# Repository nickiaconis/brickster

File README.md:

BricksTer
=========

LEGO bricks controlled from terminal.

### Notice

[BricksTer has moved to BTbricks. Please follow this link for the list of new repositories.](https://github.com/BTbricks)

#### Android GUI (based on 8879 LEGO Power Functions Speed Remote Control)

#### Android GUI (based on 8885 LEGO Power Functions Remote Control)

#### Initial Prototype Demonstration

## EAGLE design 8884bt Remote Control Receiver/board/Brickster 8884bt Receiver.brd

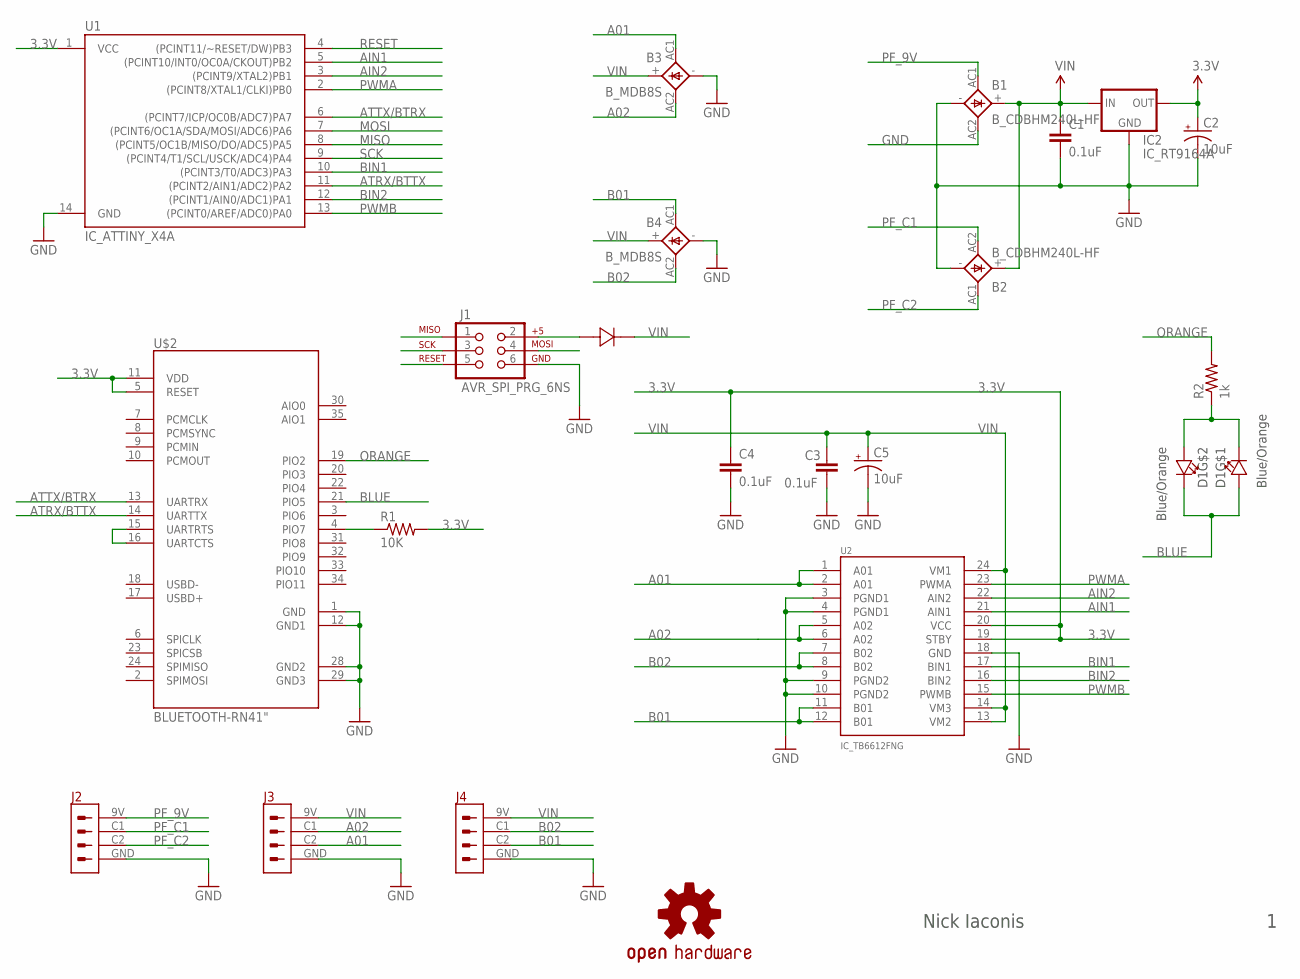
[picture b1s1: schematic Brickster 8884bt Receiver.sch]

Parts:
B1, B2: B_CDBHM240L-HF; MBS-2
B3, B4: B_MDB8S; MICRO-DIP
C1, C3, C4: 0.1uF; 0402
C2, C5: 10uF; 1206
D1: Blue/Orange; CHIP-LTST
D2: D; SOD80
IC2: IC_RT9164A; SOT223
J1: AVR_SPI_PRG_6NS; 2X3-NS
J2, J3, J4: CON_PF
LOGO1: OSHW-LOGOM; OSHW-LOGO-M
R1: 10K; 0402
R2: 1k; 0402
U1: IC_ATTINY_X4A; 14S1
U2: IC_TB6612FNG; SSOP24
U$2: BLUETOOTH-RN41"; RN41

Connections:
3.3V: C2.1 (+), C4.1, IC2.2 (OUT), R1.2, U1.1 (VCC), U2.19 (STBY), U2.20 (VCC), U$2.5 (RESET), U$2.11 (VDD)
A01: B3.AC1, J3.C2, U2.1 (A01), U2.2 (A01)
A02: B3.AC2, J3.C1, U2.5 (A02), U2.6 (A02)
AIN1: U1.5 ((PCINT10/INT0/OC0A/CKOUT)PB2), U2.21 (AIN1)
AIN2: U1.3 ((PCINT9/XTAL2)PB1), U2.22 (AIN2)
ATRX/BTTX: U1.11 ((PCINT2/AIN1/ADC2)PA2), U$2.14 (UARTTX)
ATTX/BTRX: U1.6 ((PCINT7/ICP/OC0B/ADC7)PA7), U$2.13 (UARTRX)
B01: B4.AC1, J4.C2, U2.11 (B01), U2.12 (B01)
B02: B4.AC2, J4.C1, U2.7 (B02), U2.8 (B02)
BIN1: U1.10 ((PCINT3/T0/ADC3)PA3), U2.17 (BIN1)
BIN2: U1.12 ((PCINT1/AIN0/ADC1)PA1), U2.16 (BIN2)
BLUE: D1.1, D1.4, U$2.21 (PIO5)
GND: B1.-, B1.AC2, B2.-, B3.-, B4.-, C1.2, C2.2 (-), C3.2, C4.2, C5.2 (-), IC2.1 (GND), J1.6, J2.GND, J3.GND, J4.GND, U1.14 (GND), U2.3 (PGND1), U2.4 (PGND1), U2.9 (PGND2), U2.10 (PGND2), U2.18 (GND), U$2.1 (GND), U$2.12 (GND1), U$2.28 (GND2), U$2.29 (GND3)
MISO: J1.1, U1.8 ((PCINT5/OC1B/MISO/DO/ADC5)PA5)
MOSI: J1.4, U1.7 ((PCINT6/OC1A/SDA/MOSI/ADC6)PA6)
unnamed: D2.1, J1.2
unnamed: U$2.15 (UARTRTS), U$2.16 (UARTCTS)
unnamed: R1.1, U$2.4 (PIO7)
unnamed: D1.2, D1.3, R2.1
ORANGE: R2.2, U$2.19 (PIO2)
PF_9V: B1.AC1, J2.9V
PF_C1: B2.AC2, J2.C1
PF_C2: B2.AC1, J2.C2
PWMA: U1.2 ((PCINT8/XTAL1/CLKI)PB0), U2.23 (PWMA)
PWMB: U1.13 ((PCINT0/AREF/ADC0)PA0), U2.15 (PWMB)
RESET: J1.5, U1.4 ((PCINT11/~RESET/DW)PB3)
SCK: J1.3, U1.9 ((PCINT4/T1/SCL/USCK/ADC4)PA4)
VIN: B1.+, B2.+, B3.+, B4.+, C1.1, C3.1, C5.1 (+), D2.2, IC2.3 (IN), J3.9V, J4.9V, U2.13 (VM2), U2.14 (VM3), U2.24 (VM1)

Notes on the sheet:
Nick Iaconis

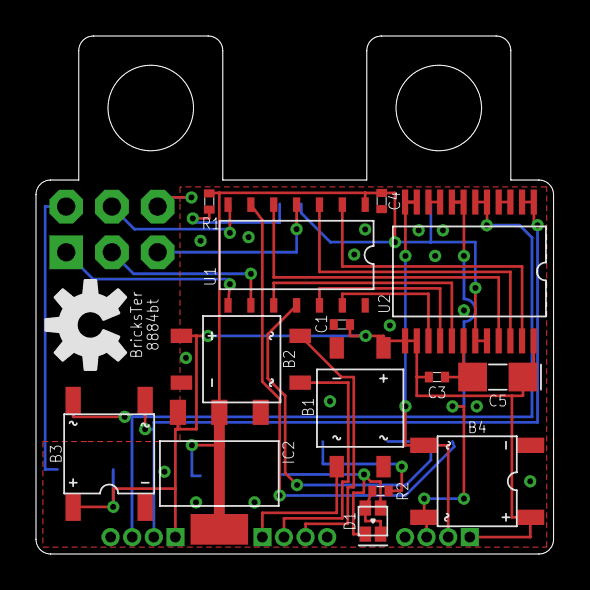
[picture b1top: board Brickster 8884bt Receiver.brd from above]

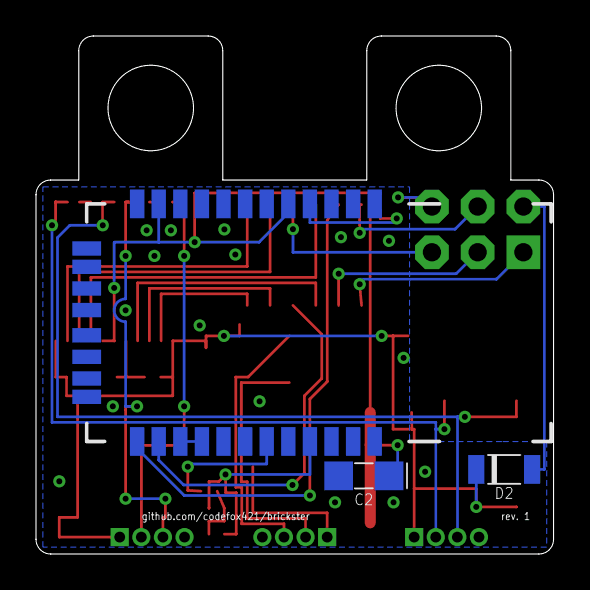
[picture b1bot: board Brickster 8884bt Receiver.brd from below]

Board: 2 copper layers, 28.8 x 28.8 mm, 22 parts (3 on the bottom side), 28 nets.

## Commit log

2013-10-02 Add schematic
2013-10-02 Add firmware
2013-10-02 Update license/readme/gitignore
2013-10-02 Reorganize 8884bt files
2013-10-02 Fix naming conventions for Arduino compatibility
2013-10-02 Clean up firmware inline docs
2013-10-04 Initial Android app
2013-10-06 Support multitouch on GUI
    8885 momentary remote control
2013-10-07 Add new GUI
    +8879 Speed Remote Control
    +Use action bar
2013-10-07 Update readme with YouTube links
    +8879 GUI demo
    +8885 GUI demo
    +Prototype demo
2013-10-08 Update schematic components +New components include device footprints
2013-10-08 Include parts library with source
2013-10-08 Prepare repository for board layout
2013-10-08 Layout PCB
    +Revision 1 (uses RN-41/42)
2013-10-09 Fix D2/Bluetooth intersection
2013-10-09 Add second mounting tab to PCB
2013-10-09 Change PF key shape
    square pad for +9V
    square shape is easier to recognize than octagon
2013-10-09 Add second mounting tab
    provides more stability
2013-10-10 Widen PF drills
2013-10-10 Mask vias
    don't stop solder mask for vias
2013-10-10 Finalize rev. 1 layout
2013-10-10 Decouple receiver from app
    Changes in the app should not affect the revision history of the
    receiver
2013-10-10 Decouple app from receiver
    changes in the receiver should not affect the revision history of the
    app
2013-10-15 Add GUI switching & motor reversing
2013-10-15 Look up menu items by id
    rather than by index
2013-10-15 Save motor reversing preferences per device
2013-10-15 Save controller preferences per device
    +add icons for switching GUIs
2013-10-19 Add BOM
2014-02-27 Enable automatic build using Maven
2014-02-27 Connect to Travis-CI
2014-02-27 Clear android history in order to merge with bluetooth-receiver into master
2014-03-19 Only build the master branch
2014-03-19 Remove readme from android branch
2014-03-19 Add readme to master branch
2014-05-01 Enable multiple simultaneous connections
    First pass -- works, but needs some TLC
2014-06-25 Increase scalability of momentary remote UI
2014-06-26 Don't set view before verifying Bluetooth
    Also remove trailing whitespace
2014-06-26 Don't initialize/find views until necessary
2014-06-26 Use appropriately sized bitmaps
2014-06-26 Tweak momentary image width
2014-07-16 Update README.md
    Forward traffic to new organization page.

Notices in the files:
parts and their libraries:
SparkFun-RF: Licensing: CC v3.0 Share-Alike You are welcome to use this library for commercial purposes.
